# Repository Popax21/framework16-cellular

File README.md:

# Framework Laptop 16 M.2 Cellular Modem Expansion Bay Module

> [!IMPORTANT]
> ### This design is still a work-in-progress, and should currently be considered non-functional!
>
> The current revision contained in this repository (v1.1) still has some glaring design defects, and as such will need at least one more revision to fully bug-fix.
> As of now I am focusing on other projects, so there is no timeline for when development of the module will resume.

This repository holds the WIP design files for a module for the Framework Laptop 16's Expansion Bay allowing for the connection of a standard M.2 B-Key cellular modem, also featuring a microSIM connector for the insertion of a standard SIM card.
It was designed for usage with Quectel RM50X / RM5X0-series 5G modules, but other 3.7V-tolerant modules are expected to work as well.

> [!WARNING]
> This module provides the M.2 slot with a VCC of 3.7V, and not the standard 3.3V!
> This is the recommended voltage of the Quectel modems the module is designed around, but you may have to adapt the schematic in case you want to use a different module.

The module provides the M.2 slot with both a PCI-E x1 interface as well as an USB2 HS (max 480Mbps) interface, however routing priority has been given to the PCI-E lane, so the full bandwith may not be available over the USB port.
Note that no USB3.x interface has been routed to the slot!
This means that in practice you should be able to use any M.2 cellular module, however only PCI-E capable modules will be able to provide high-speed connectivity.

> [!NOTE]
> This design decision is rooted in the Expanion Bay's interface to the rest of the computer, which only provides a single USB2 port for modules to use.
> Providing a full USB 3.0 (or higher) interface for the modem would have required the addition of a PCI-E USB host controller, which would have in turn complicated the PCI-E logic since now two separate REFCLK signals would be required.
> While there is support for receiving two separate REFCLKs from the mainboard since hardware revision 7, no such support was implemented to reduce the design complexity of the module.

Some functionality exposed by the board (i.e. hardware rfkill/airplane mode, modem resets / power-on shutdowns) are exposed behind an I2C GPIO port, and will require support from the Framework Laptop 16's EC (Embedded Controller) MCU to fully operate.
No such support has been developed as of now, however such support is planned to be released at a future date in the form of firmware patches.

All Expansion Bay modules feature an EEPROM which holds a "descriptor" for the installed module, which contains, among other things, the module's serial number as well as GPIO configuration.
By default the module should be picked as a Dual M.2 Expansion module until an appropriate descriptor has been written onto the EEPROM.
The PCB has been designed to still operate when treated as such an expansion module, however a proper custom EEPROM descriptor will be developed at a future date as part of EC integration.

No pre-packaged schematics / Gerber files are available at the moment, but a GH Actions pipeline may be set up at a future date.

> [!IMPORTANT]
> If you still plan on ordering a PCB through e.g. JLCPCB, ensure that you enable Impedance Matching and specifically select stackup JLC041611H-3313 as part of the checkout process.
> This stackup is required for the sensitive PCI-E / USB / RF signals to be properly impedance matched and not be distorted.

This design uses modified versions of the template PCB and FX Beam connector symbol / footprint published by jyancat, found [here](https://github.com/jyancat/ExpansionBay/tree/main/Electrical/KiCad_templates/Expansion_Bay).

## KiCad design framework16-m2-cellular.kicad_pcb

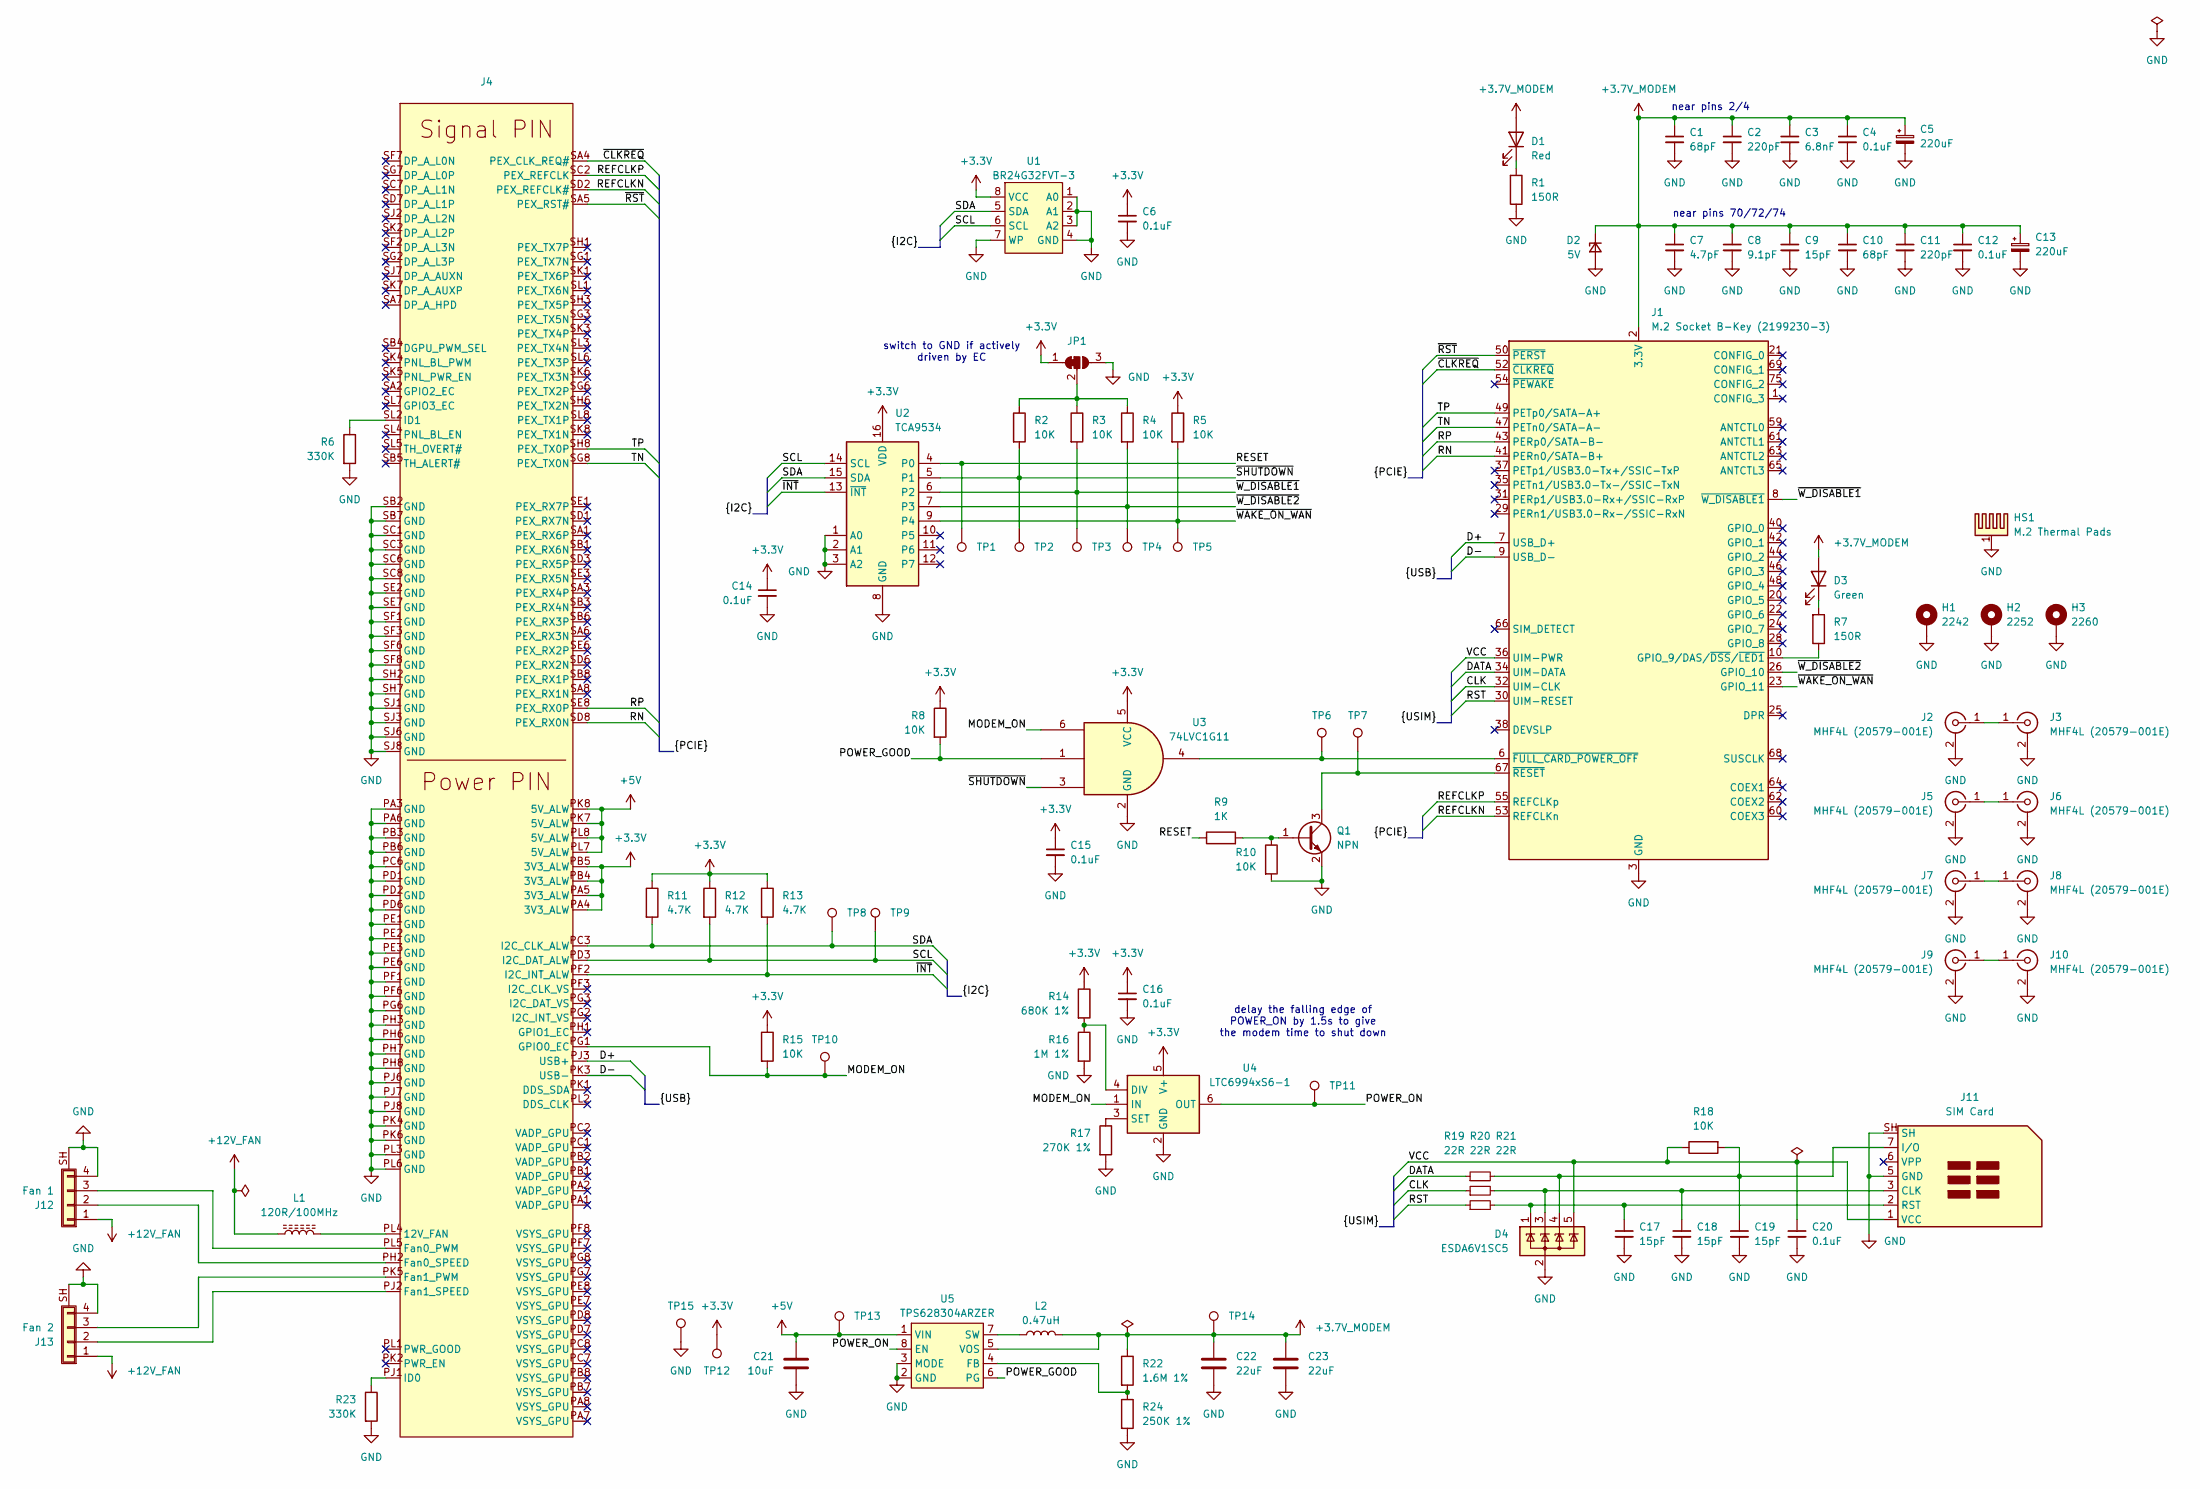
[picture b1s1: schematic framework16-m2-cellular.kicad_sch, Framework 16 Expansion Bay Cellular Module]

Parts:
C1, C10: 68pF; C_0603_1608Metric; LCSC C62782
C2, C11: 220pF; C_0603_1608Metric; LCSC C106210
C3: 6.8nF; C_0603_1608Metric; LCSC C162241
C4, C6, C12, C14, C15, C16, C20: 0.1uF; C_0603_1608Metric; LCSC C14663
C5, C13: 220uF; CP_Elec_6.3x5.4; LCSC C72494
C7: 4.7pF; C_0603_1608Metric; LCSC C1669
C8: 9.1pF; C_0603_1608Metric; LCSC C61817
C9, C17, C18, C19: 15pF; C_0603_1608Metric; LCSC C1644
C21: 10uF; C_0603_1608Metric; LCSC C19702
C22, C23: 22uF; C_1206_3216Metric; LCSC C90146
D1: Red; LED_0805_2012Metric; LCSC C94741
D2: 5V; D_SOD-523; LCSC C20932
D3: Green; LED_0805_2012Metric; LCSC C2297
D4: ESDA6V1SC5; SOT-23-5; LCSC C2935146
H1: 2242; MountingHole_2.2mm_M2_Pad
H2: 2252; MountingHole_2.2mm_M2_Pad
H3: 2260; MountingHole_2.2mm_M2_Pad
HS1: M.2 Thermal Pads; Thermal Pad
J1: M.2 Socket B-Key (2199230-3); CONN67_2199230_TEC; LCSC C590859
J2, J5, J7, J9: MHF4L (20579-001E); CONN_20579-001E_IPX; LCSC C434808
J3, J6, J8, J10: MHF4L (20579-001E); CONN_20579-001E_IPX; LCSC C5881005
J4: Expansion Bay FXBeam
J11: SIM Card; microSIM_JAE_SF53S006VCBR2000; LCSC C2929301
J12: Fan 1; AFC30-S04FCC-00; LCSC C395232
J13: Fan 2; AFC30-S04FCC-00; LCSC C395232
JP1: SolderJumper_3_Bridged12; SolderJumper-3_P1.3mm_Bridged12_RoundedPad1.0x1.5mm
L1: 120R/100MHz; R_0603_1608Metric; LCSC C14709
L2: 0.47uH; L_1008_2520Metric; LCSC C519277
Q1: NPN; SOT-23; LCSC C916392
R1, R7: 150R; R_0603_1608Metric; LCSC C22808
R2, R3, R4, R5, R8, R10, R15, R18: 10K; R_0603_1608Metric; LCSC C25804
R6, R23: 330K; R_0603_1608Metric; LCSC C23137
R9: 1K; R_0603_1608Metric; LCSC C21190
R11, R12, R13: 4.7K; R_0603_1608Metric; LCSC C23162
R14: 680K 1%; R_0603_1608Metric; LCSC C25822
R16: 1M 1%; R_0603_1608Metric; LCSC C22935
R17: 270K 1%; R_0603_1608Metric; LCSC C22965
R19, R20, R21: 22R; R_0603_1608Metric; LCSC C23345
R22: 1.6M 1%; R_0805_2012Metric; LCSC C5121530
R24: 250K 1%; R_0805_2012Metric; LCSC C5156563
TP1, TP2, TP3, TP4, TP5, TP6, TP7, TP8, TP9, TP10, TP11, TP12, TP13, TP14, TP15: TestPoint; TestPoint_Pad_D1.0mm
U1: BR24G32FVT-3; TSSOP-8_4.4x3mm_P0.65mm; LCSC C2061284
U2: TCA9534; TSSOP-16_4.4x5mm_P0.65mm; LCSC C783615
U3: 74LVC1G11; SOT-23-6; LCSC C22356918
U4: LTC6994xS6-1; TSOT-23-6; LCSC C581054
U5: TPS628304ARZER; WQFN-HR8_RZE_TEX; LCSC C33092582

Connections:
+3.3V: C6.1, C14.1, C15.1, C16.1, J4.PA4 (3V3_ALW), J4.PA5 (3V3_ALW), J4.PB4 (3V3_ALW), J4.PB5 (3V3_ALW), JP1.1 (A), R5.1, R8.1, R11.1, R12.1, R13.1, R14.1, R15.1, TP12.1, U1.8 (VCC), U2.16 (VDD), U3.5 (VCC), U4.5 (V+)
+3.7V_MODEM: C1.1, C2.1, C3.1, C4.1, C5.1, C7.1, C8.1, C9.1, C10.1, C11.1, C12.1, C13.1, C22.1, C23.1, D1.2 (A), D2.1 (K), D3.2 (A), J1.2 (3.3V), J1.4 (3.3V), J1.70 (3.3V), J1.72 (3.3V), J1.74 (3.3V), L2.2, R22.1, TP14.1, U5.5 (VOS)
+5V: C21.1, J4.PK7 (5V_ALW), J4.PK8 (5V_ALW), J4.PL7 (5V_ALW), J4.PL8 (5V_ALW), TP13.1, U5.1 (VIN)
+12V_FAN: J12.1, J13.1, L1.1
/CLK: J1.32 (UIM-CLK), R20.1
/D+: J1.7 (USB_D+), J4.PJ3 (USB+)
/D-: J1.9 (USB_D-), J4.PK3 (USB-)
/DATA: J1.34 (UIM-DATA), R19.1
/MODEM_ON: J4.PG1 (GPIO0_EC), R15.2, TP10.1, U3.6, U4.1 (IN)
/POWER_GOOD: R8.2, U3.1, U5.6 (PG)
/POWER_ON: TP11.1, U4.6 (OUT), U5.8 (EN)
/REFCLKN: J1.53 (REFCLKn), J4.SD2 (PEX_REFCLK#)
/REFCLKP: J1.55 (REFCLKp), J4.SC2 (PEX_REFCLK)
/RESET: R9.1, TP1.1, U2.4 (P0)
/RN: J1.41 (PERn0/SATA-B+), J4.SD8 (PEX_RX0N)
/RP: J1.43 (PERp0/SATA-B-), J4.SE8 (PEX_RX0P)
/RST: J1.30 (UIM-RESET), R21.1
/SCL: J4.PD3 (I2C_DAT_ALW), R12.2, TP9.1, U1.6 (SCL), U2.14 (SCL)
/SDA: J4.PC3 (I2C_CLK_ALW), R11.2, TP8.1, U1.5 (SDA), U2.15 (SDA)
/TN: J1.47 (PETn0/SATA-A-), J4.SG8 (PEX_TX0N)
/TP: J1.49 (PETp0/SATA-A+), J4.SH8 (PEX_TX0P)
/VCC: C20.1, D4.5 (K), J1.36 (UIM-PWR), J11.1 (VCC), R18.1
/~CLKREQ: J1.52 (~CLKREQ), J4.SA4 (PEX_CLK_REQ#)
/~INT: J4.PF2 (I2C_INT_ALW), R13.2, U2.13 (~INT)
/~RST: J1.50 (~PERST), J4.SA5 (PEX_RST#)
/~SHUTDOWN: R2.2, TP2.1, U2.5 (P1), U3.3
/~WAKE_ON_WAN: J1.23 (GPIO_11), R5.2, TP5.1, U2.9 (P4)
/~W_DISABLE1: J1.8 (~W_DISABLE1), R3.2, TP3.1, U2.6 (P2)
/~W_DISABLE2: J1.26 (GPIO_10), R4.2, TP4.1, U2.7 (P3)
GND: C1.2, C2.2, C3.2, C4.2, C5.2, C6.2, C7.2, C8.2, C9.2, C10.2, C11.2, C12.2, C13.2, C14.2, C15.2, C16.2, C17.2, C18.2, C19.2, C20.2, C21.2, C22.2, C23.2, D2.2 (A), D4.2 (A), H1.1, H2.1, H3.1, HS1.1, J1.3 (GND), J1.5 (GND), J1.11 (GND), J1.27 (GND), J1.33 (GND), J1.39 (GND), J1.45 (GND), J1.51 (GND), J1.57 (GND), J1.71 (GND), J1.73 (GND), J2.2 (Ext), J3.2 (Ext), J4.PA3 (GND), J4.PA6 (GND), J4.PB3 (GND), J4.PB6 (GND), J4.PC6 (GND), J4.PD1 (GND), J4.PD2 (GND), J4.PD6 (GND), J4.PE1 (GND), J4.PE2 (GND), J4.PE3 (GND), J4.PE6 (GND), J4.PF1 (GND), J4.PF6 (GND), J4.PG6 (GND), J4.PH3 (GND), J4.PH6 (GND), J4.PH7 (GND), J4.PH8 (GND), J4.PJ6 (GND), J4.PJ7 (GND), J4.PJ8 (GND), J4.PK4 (GND), J4.PK6 (GND), J4.PL3 (GND), J4.PL6 (GND), J4.SB2 (GND), J4.SB7 (GND), J4.SC1 (GND), J4.SC3 (GND), J4.SC6 (GND), J4.SC8 (GND), J4.SE2 (GND), J4.SE7 (GND), J4.SF1 (GND), J4.SF3 (GND), J4.SF6 (GND), J4.SF8 (GND), J4.SH2 (GND), J4.SH7 (GND), J4.SJ1 (GND), J4.SJ3 (GND), J4.SJ6 (GND), J4.SJ8 (GND), J5.2 (Ext), J6.2 (Ext), J7.2 (Ext), J8.2 (Ext), J9.2 (Ext), J10.2 (Ext), J11.5 (GND), J11.SH, J12.4, J12.SH (Shield), J13.4, J13.SH (Shield), JP1.3 (B), Q1.2 (E), R1.1, R6.2, R10.2, R16.2, R17.2, R23.2, R24.2, TP15.1, U1.1 (A0), U1.2 (A1), U1.3 (A2), U1.4 (GND), U1.7 (WP), U2.1 (A0), U2.2 (A1), U2.3 (A2), U2.8 (GND), U3.2 (GND), U4.2 (GND), U5.2 (GND), U5.3 (MODE); also elsewhere on the board
unnamed: D1.1 (K), R1.2
unnamed: D3.1 (K), R7.2
unnamed: J1.10 (GPIO_9/DAS/~DSS/~LED1), R7.1
unnamed: J1.6 (~FULL_CARD_POWER_OFF), TP6.1, U3.4
unnamed: J1.67 (~RESET), Q1.3 (C), TP7.1
unnamed: J2.1 (In), J3.1 (In)
unnamed: J4.PL4 (12V_FAN), L1.2
unnamed: J4.PJ1 (ID0), R23.1
unnamed: J4.SL2 (ID1), R6.1
unnamed: J5.1 (In), J6.1 (In)
unnamed: J7.1 (In), J8.1 (In)
unnamed: J9.1 (In), J10.1 (In)
unnamed: C18.1, D4.3 (K), J11.3 (CLK), R20.2
unnamed: C19.1, D4.4 (K), J11.7 (I/O), R18.2, R19.2
unnamed: C17.1, D4.1 (K), J11.2 (RST), R21.2
unnamed: J4.PH2 (Fan0_SPEED), J12.2
unnamed: J4.PL5 (Fan0_PWM), J12.3
unnamed: J4.PJ2 (Fan1_SPEED), J13.2
unnamed: J4.PK5 (Fan1_PWM), J13.3
unnamed: JP1.2 (C), R2.1, R3.1, R4.1
unnamed: Q1.1 (B), R9.2, R10.1
unnamed: R14.2, R16.1, U4.4 (DIV)
unnamed: R17.1, U4.3 (SET)
unnamed: R22.2, R24.1, U5.4 (FB)
unnamed: L2.1, U5.7 (SW)

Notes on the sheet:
delay the falling edge of POWER_ON by 1.5s to give the modem time to shut down
near pins 70/72/74
near pins 2/4
switch to GND if actively driven by EC

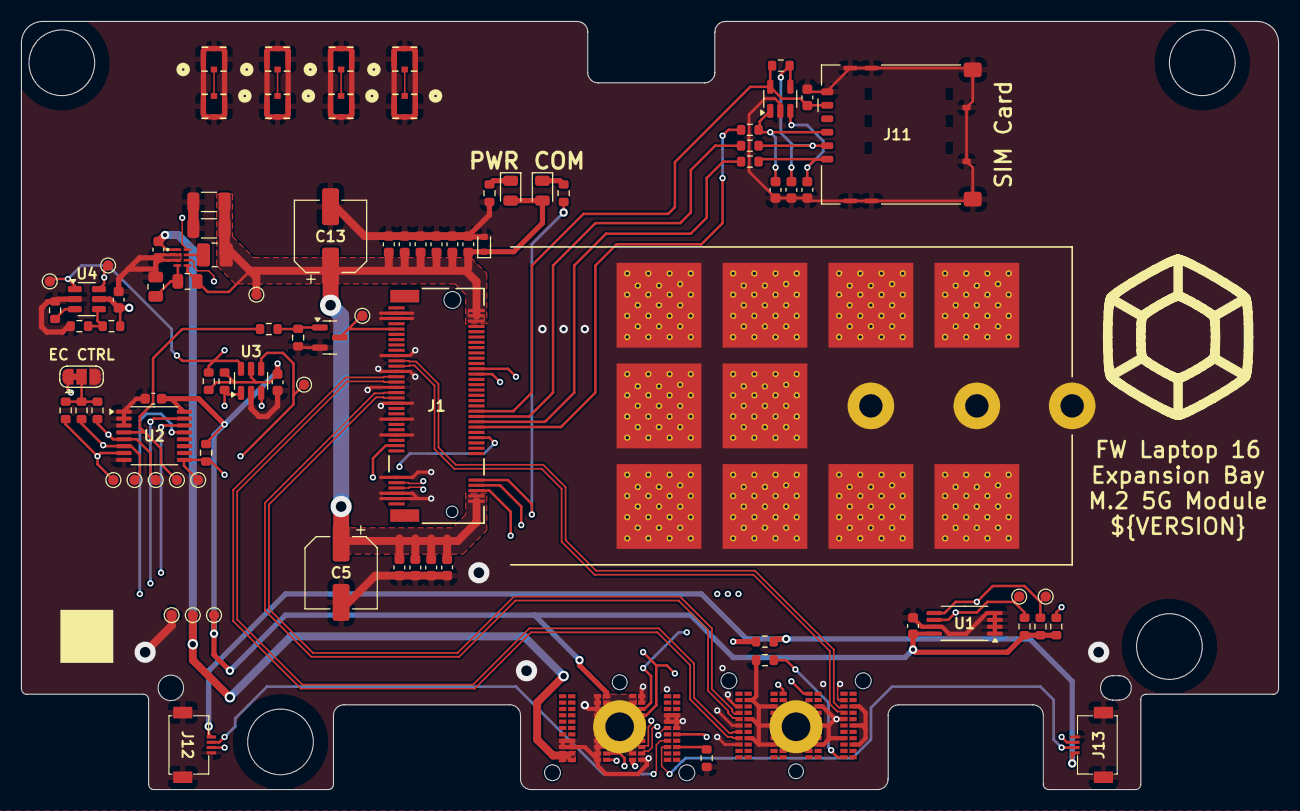
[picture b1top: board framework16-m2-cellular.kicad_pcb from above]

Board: 4 copper layers, 118.7 x 72.5 mm, 101 parts (0 on the bottom side), 55 nets.

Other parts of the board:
HS1#2, HS1#3, HS1#4, HS1#5, HS1#6, HS1#7, HS1#8, HS1#9, HS1#10: M.2 Thermal Pads; Thermal Pad

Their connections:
GND: HS1#2.1, HS1#3.1, HS1#4.1, HS1#5.1, HS1#6.1, HS1#7.1, HS1#8.1, HS1#9.1, HS1#10.1; also elsewhere on the board

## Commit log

2025-06-01 Version v1.0
2025-06-01 Version v1.1
2025-06-01 Add README
2025-06-01 Add LICENSE.txt
2025-06-01 Minor README fixes
2025-06-04 Bunch of improvements for v1.1
2025-06-11 Fixes from v1.1
    TODO: check the orientation of the fan headers
2025-09-01 Remove EEPROM address jumper
2025-09-01 Fix flipped fan connector
2025-09-01 Fix incorrect fan header description
2025-09-01 Random KiCAD changes
2025-10-22 Add solder pads for screw standoffs
2025-11-03 Swap out capacitors with more low profile ones
2026-02-01 Add current project status disclaimer
